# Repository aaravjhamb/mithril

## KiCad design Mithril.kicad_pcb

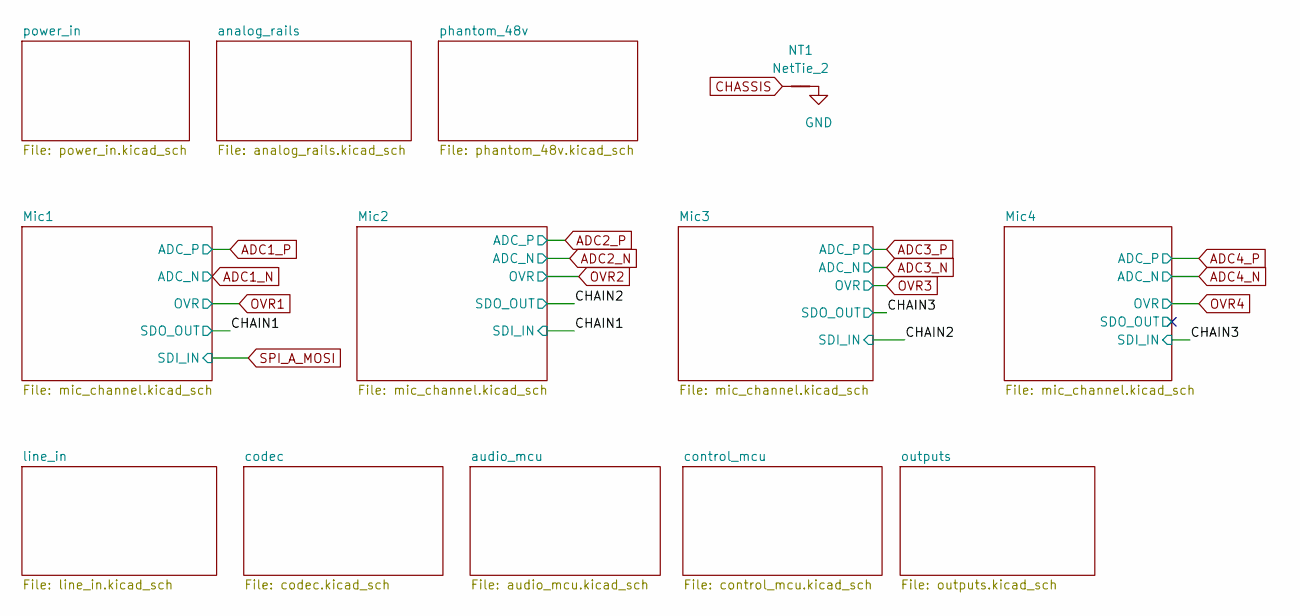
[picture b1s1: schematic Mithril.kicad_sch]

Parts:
NT1: NetTie_2; NetTie-2_SMD_Pad0.5mm

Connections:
CHASSIS: NT1.1; also elsewhere on the board
GND: NT1.2; also elsewhere on the board

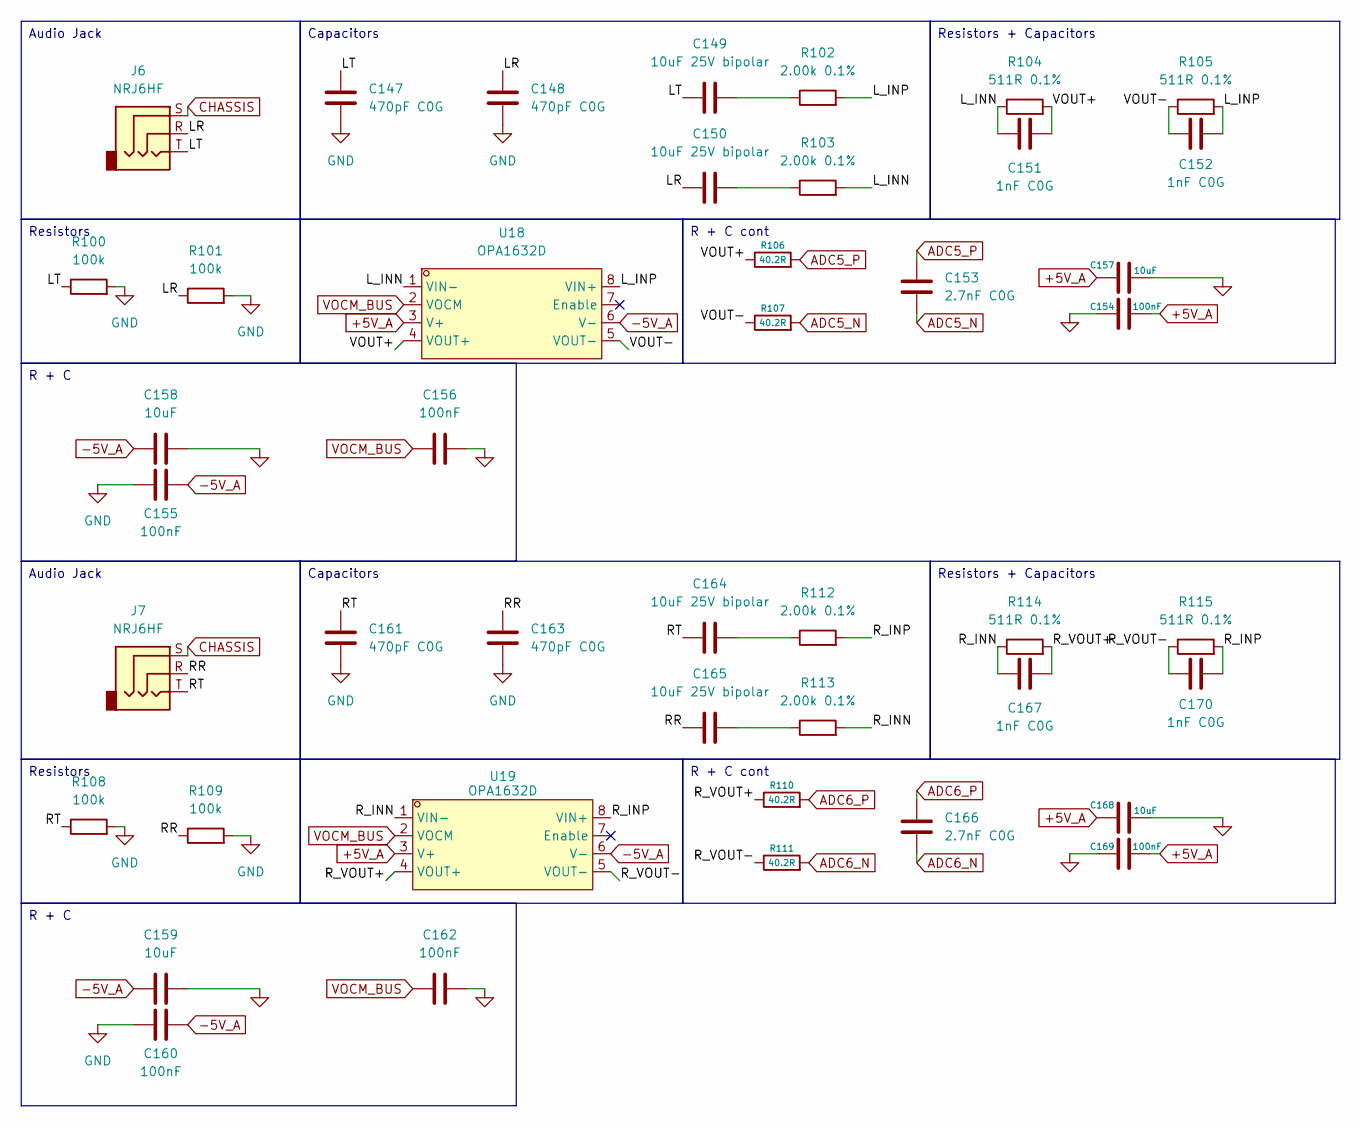
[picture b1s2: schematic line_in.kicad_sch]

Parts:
C147, C148, C161, C163: 470pF C0G; C_0603_1608Metric
C149, C150, C164, C165: 10uF 25V bipolar; CP_Elec_6.3x5.4
C151, C152, C167, C170: 1nF C0G; C_0603_1608Metric
C153, C166: 2.7nF C0G; C_0603_1608Metric
C154, C155, C156, C160, C162, C169: 100nF; C_0603_1608Metric
C157, C158, C159, C168: 10uF; C_0805_2012Metric
J6, J7: NRJ6HF; Jack_6.35mm_Neutrik_NRJ6HF_Horizontal
R100, R101, R108, R109: 100k; R_0603_1608Metric
R102, R103, R112, R113: 2.00k 0.1%; R_0603_1608Metric
R104, R105, R114, R115: 511R 0.1%; R_0603_1608Metric
R106, R107, R110, R111: 40.2R; R_0603_1608Metric
U18, U19: OPA1632D; SOIC-8_L4.9-W3.9-P1.27-LS6.0-BL; MPN OPA1632DR; LCSC Part C86715

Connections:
+5V_A: C154.2, C157.1, C168.1, C169.2, U18.3 (V+), U19.3 (V+); also elsewhere on the board
/line_in/LR: C148.1, C150.1, J6.R, R101.1
/line_in/LT: C147.1, C149.1, J6.T, R100.1
/line_in/L_INN: C151.1, R103.2, R104.1, U18.1 (VIN-)
/line_in/L_INP: C152.2, R102.2, R105.2, U18.8 (VIN+)
/line_in/RR: C163.1, C165.1, J7.R, R109.1
/line_in/RT: C161.1, C164.1, J7.T, R108.1
/line_in/R_INN: C167.1, R113.2, R114.1, U19.1 (VIN-)
/line_in/R_INP: C170.2, R112.2, R115.2, U19.8 (VIN+)
/line_in/R_VOUT+: C167.2, R110.1, R114.2, U19.4 (VOUT+)
/line_in/R_VOUT-: C170.1, R111.1, R115.1, U19.5 (VOUT-)
/line_in/VOUT+: C151.2, R104.2, R106.1, U18.4 (VOUT+)
/line_in/VOUT-: C152.1, R105.1, R107.1, U18.5 (VOUT-)
ADC5_N: C153.2, R107.2; also elsewhere on the board
ADC5_P: C153.1, R106.2; also elsewhere on the board
ADC6_N: C166.2, R111.2; also elsewhere on the board
ADC6_P: C166.1, R110.2; also elsewhere on the board
CHASSIS: J6.S, J7.S; also elsewhere on the board
GND: C147.2, C148.2, C154.1, C155.1, C156.2, C157.2, C158.2, C159.2, C160.1, C161.2, C162.2, C163.2, C168.2, C169.1, R100.2, R101.2, R108.2, R109.2; also elsewhere on the board
unnamed: C149.2, R102.1
unnamed: C150.2, R103.1
unnamed: C164.2, R112.1
unnamed: C165.2, R113.1
VOCM_BUS: C156.1, C162.1, U18.2 (VOCM), U19.2 (VOCM); also elsewhere on the board
−5V_A: C155.2, C158.1, C159.1, C160.2, U18.6 (V-), U19.6 (V-); also elsewhere on the board

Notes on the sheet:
Audio Jack
Capacitors
R + C cont
R + C
Resistors + Capacitors
Resistors

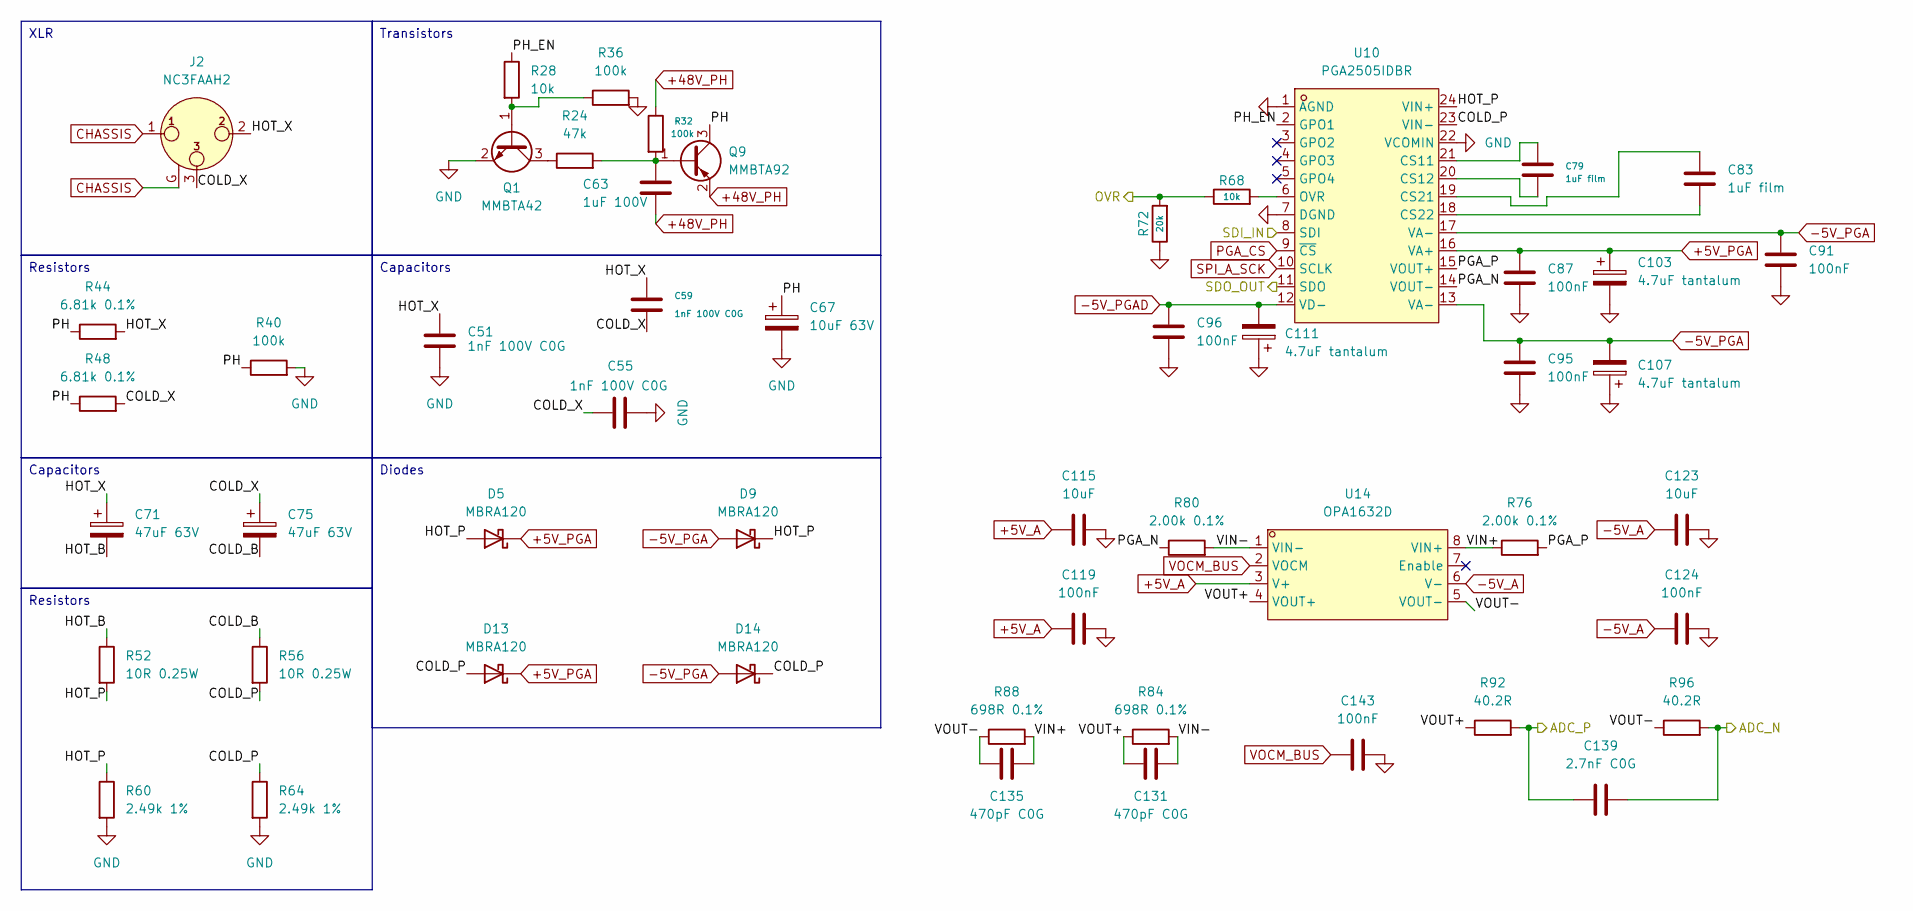
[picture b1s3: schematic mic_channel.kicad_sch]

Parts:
C51, C55, C59: 1nF 100V C0G; C_0603_1608Metric
C63: 1uF 100V; C_1206_3216Metric
C67: 10uF 63V; CP_Elec_6.3x7.7
C71, C75: 47uF 63V; CP_Elec_8x10.5
C79, C83: 1uF film; C_1210_3225Metric
C87, C91, C95, C96, C119, C124, C143: 100nF; C_0603_1608Metric
C103, C107, C111: 4.7uF tantalum; CP_EIA-3216-18_Kemet-A
C115, C123: 10uF; C_0805_2012Metric
C131, C135: 470pF C0G; C_0603_1608Metric
C139: 2.7nF C0G; C_0603_1608Metric
D5, D9, D13, D14: MBRA120; D_SMA
J2: NC3FAAH2; Jack_XLR_Neutrik_NC3FAAH2_Horizontal; LCSC Part C368522
Q1: MMBTA42; SOT-23
Q9: MMBTA92; SOT-23
R24: 47k; R_0805_2012Metric
R28: 10k; R_0805_2012Metric
R32, R36, R40: 100k; R_0805_2012Metric
R44, R48: 6.81k 0.1%; R_1206_3216Metric
R52, R56: 10R 0.25W; R_1206_3216Metric
R60, R64: 2.49k 1%; R_0603_1608Metric
R68: 10k; R_0603_1608Metric
R72: 20k; R_0603_1608Metric
R76, R80: 2.00k 0.1%; R_0603_1608Metric
R84, R88: 698R 0.1%; R_0603_1608Metric
R92, R96: 40.2R; R_0603_1608Metric
U10: PGA2505IDBR; SSOP-24_L8.2-W5.3-P0.65-LS7.8-BL; MPN PGA2505IDBR; LCSC Part C2877465
U14: OPA1632D; SOIC-8_L4.9-W3.9-P1.27-LS6.0-BL; MPN OPA1632DR; LCSC Part C86715

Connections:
+5V_A: C115.1, C119.1, U14.3 (V+); also elsewhere on the board
+5V_PGA: C87.1, C103.1, D5.1 (K), D13.1 (K), U10.16 (VA+); also elsewhere on the board
+48V_PH: C63.2, Q9.2 (E), R32.1; also elsewhere on the board
/CHAIN1: U10.11 (SDO); also elsewhere on the board
/Mic1/COLD_B: C75.2, R56.1
/Mic1/COLD_P: D13.2 (A), D14.1 (K), R56.2, R64.1, U10.23 (VIN-)
/Mic1/COLD_X: C55.1, C59.2, C75.1, J2.3, R48.2
/Mic1/HOT_B: C71.2, R52.1
/Mic1/HOT_P: D5.2 (A), D9.1 (K), R52.2, R60.1, U10.24 (VIN+)
/Mic1/HOT_X: C51.1, C59.1, C71.1, J2.2, R44.2
/Mic1/PGA_N: R80.1, U10.14 (VOUT-)
/Mic1/PGA_P: R76.2, U10.15 (VOUT+)
/Mic1/PH: C67.1, Q9.3 (C), R40.1, R44.1, R48.1
/Mic1/PH_EN: R28.1, U10.2 (GPO1)
/Mic1/VIN+: C135.1, R76.1, R88.2, U14.8 (VIN+)
/Mic1/VIN-: C131.2, R80.2, R84.2, U14.1 (VIN-)
/Mic1/VOUT+: C131.1, R84.1, R92.1, U14.4 (VOUT+)
/Mic1/VOUT-: C135.2, R88.1, R96.1, U14.5 (VOUT-)
ADC1_N: C139.2, R96.2; also elsewhere on the board
ADC1_P: C139.1, R92.2; also elsewhere on the board
CHASSIS: J2.1, J2.G; also elsewhere on the board
GND: C51.2, C55.2, C67.2, C87.2, C91.2, C95.2, C96.2, C103.2, C107.1, C111.1, C115.2, C119.2, C123.2, C124.2, C143.2, Q1.2 (E), R36.2, R40.2, R60.2, R64.2, R72.1, U10.1 (AGND), U10.7 (DGND), U10.22 (VCOMIN); also elsewhere on the board
unnamed: Q1.1 (B), R28.2, R36.1
unnamed: Q1.3 (C), R24.1
unnamed: C63.1, Q9.1 (B), R24.2, R32.2
unnamed: C79.1, U10.21 (CS11)
unnamed: C79.2, U10.20 (CS12)
unnamed: C83.1, U10.19 (CS21)
unnamed: C83.2, U10.18 (CS22)
unnamed: R68.2, U10.6 (OVR)
OVR1: R68.1, R72.2; also elsewhere on the board
PGA_CS: U10.9 (~CS); also elsewhere on the board
SPI_A_MOSI: U10.8 (SDI); also elsewhere on the board
SPI_A_SCK: U10.10 (SCLK); also elsewhere on the board
VOCM_BUS: C143.1, U14.2 (VOCM); also elsewhere on the board
−5V_A: C123.1, C124.1, U14.6 (V-); also elsewhere on the board
−5V_PGA: C91.1, C95.1, C107.2, D9.2 (A), D14.2 (A), U10.13 (VA-), U10.17 (VA-); also elsewhere on the board
−5V_PGAD: C96.1, C111.2, U10.12 (VD-); also elsewhere on the board

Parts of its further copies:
C52, C53, C54, C56, C57, C58, C60, C61, C62: 1nF 100V C0G; C_0603_1608Metric
C64, C65, C66: 1uF 100V; C_1206_3216Metric
C68, C69, C70: 10uF 63V; CP_Elec_6.3x7.7
C72, C73, C74, C76, C77, C78: 47uF 63V; CP_Elec_8x10.5
C80, C81, C82, C84, C85, C86: 1uF film; C_1210_3225Metric
C88, C89, C90, C92, C93, C94, C97, C98, C99, C100, C101, C102, C120, C121, C122, C126, C128, C130, C144, C145, C146: 100nF; C_0603_1608Metric
C104, C105, C106, C108, C109, C110, C112, C113, C114: 4.7uF tantalum; CP_EIA-3216-18_Kemet-A
C116, C117, C118, C125, C127, C129: 10uF; C_0805_2012Metric
C132, C133, C134, C136, C137, C138: 470pF C0G; C_0603_1608Metric
C140, C141, C142: 2.7nF C0G; C_0603_1608Metric
D6, D7, D8, D10, D11, D12, D15, D16, D17, D18, D19, D20: MBRA120; D_SMA
J3, J4, J5: NC3FAAH2; Jack_XLR_Neutrik_NC3FAAH2_Horizontal; LCSC Part C368522
Q2, Q3, Q4: MMBTA42; SOT-23
Q10, Q11, Q12: MMBTA92; SOT-23
R25, R26, R27: 47k; R_0805_2012Metric
R29, R30, R31: 10k; R_0805_2012Metric
R33, R34, R35, R37, R38, R39, R41, R42, R43: 100k; R_0805_2012Metric
R45, R46, R47, R49, R50, R51: 6.81k 0.1%; R_1206_3216Metric
R53, R54, R55, R57, R58, R59: 10R 0.25W; R_1206_3216Metric
R61, R62, R63, R65, R66, R67: 2.49k 1%; R_0603_1608Metric
R69, R70, R71: 10k; R_0603_1608Metric
R73, R74, R75: 20k; R_0603_1608Metric
R77, R78, R79, R81, R82, R83: 2.00k 0.1%; R_0603_1608Metric
R85, R86, R87, R89, R90, R91: 698R 0.1%; R_0603_1608Metric
R93, R94, R95, R97, R98, R99: 40.2R; R_0603_1608Metric
U11, U12, U13: PGA2505IDBR; SSOP-24_L8.2-W5.3-P0.65-LS7.8-BL; MPN PGA2505IDBR; LCSC Part C2877465
U15, U16, U17: OPA1632D; SOIC-8_L4.9-W3.9-P1.27-LS6.0-BL; MPN OPA1632DR; LCSC Part C86715

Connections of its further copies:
+5V_A: C116.1, C117.1, C118.1, C120.1, C121.1, C122.1, U15.3 (V+), U16.3 (V+), U17.3 (V+); also elsewhere on the board
+5V_PGA: C88.1, C89.1, C90.1, C104.1, C105.1, C106.1, D6.1 (K), D7.1 (K), D8.1 (K), D15.1 (K), D17.1 (K), D19.1 (K), U11.16 (VA+), U12.16 (VA+), U13.16 (VA+); also elsewhere on the board
+48V_PH: C64.2, C65.2, C66.2, Q10.2 (E), Q11.2 (E), Q12.2 (E), R33.1, R34.1, R35.1; also elsewhere on the board
/CHAIN1: U11.8 (SDI); also elsewhere on the board
/CHAIN2: U11.11 (SDO), U12.8 (SDI)
/CHAIN3: U12.11 (SDO), U13.8 (SDI)
/Mic2/COLD_B: C76.2, R57.1
/Mic2/COLD_P: D15.2 (A), D16.1 (K), R57.2, R65.1, U11.23 (VIN-)
/Mic2/COLD_X: C56.1, C60.2, C76.1, J3.3, R49.2
/Mic2/HOT_B: C72.2, R53.1
/Mic2/HOT_P: D6.2 (A), D10.1 (K), R53.2, R61.1, U11.24 (VIN+)
/Mic2/HOT_X: C52.1, C60.1, C72.1, J3.2, R45.2
/Mic2/PGA_N: R81.1, U11.14 (VOUT-)
/Mic2/PGA_P: R77.2, U11.15 (VOUT+)
/Mic2/PH: C68.1, Q10.3 (C), R41.1, R45.1, R49.1
/Mic2/PH_EN: R29.1, U11.2 (GPO1)
/Mic2/VIN+: C136.1, R77.1, R89.2, U15.8 (VIN+)
/Mic2/VIN-: C132.2, R81.2, R85.2, U15.1 (VIN-)
/Mic2/VOUT+: C132.1, R85.1, R93.1, U15.4 (VOUT+)
/Mic2/VOUT-: C136.2, R89.1, R97.1, U15.5 (VOUT-)
/Mic3/COLD_B: C77.2, R58.1
/Mic3/COLD_P: D17.2 (A), D18.1 (K), R58.2, R66.1, U12.23 (VIN-)
/Mic3/COLD_X: C57.1, C61.2, C77.1, J4.3, R50.2
/Mic3/HOT_B: C73.2, R54.1
/Mic3/HOT_P: D7.2 (A), D11.1 (K), R54.2, R62.1, U12.24 (VIN+)
/Mic3/HOT_X: C53.1, C61.1, C73.1, J4.2, R46.2
/Mic3/PGA_N: R82.1, U12.14 (VOUT-)
/Mic3/PGA_P: R78.2, U12.15 (VOUT+)
/Mic3/PH: C69.1, Q11.3 (C), R42.1, R46.1, R50.1
/Mic3/PH_EN: R30.1, U12.2 (GPO1)
/Mic3/VIN+: C137.1, R78.1, R90.2, U16.8 (VIN+)
/Mic3/VIN-: C133.2, R82.2, R86.2, U16.1 (VIN-)
/Mic3/VOUT+: C133.1, R86.1, R94.1, U16.4 (VOUT+)
/Mic3/VOUT-: C137.2, R90.1, R98.1, U16.5 (VOUT-)
/Mic4/COLD_B: C78.2, R59.1
/Mic4/COLD_P: D19.2 (A), D20.1 (K), R59.2, R67.1, U13.23 (VIN-)
/Mic4/COLD_X: C58.1, C62.2, C78.1, J5.3, R51.2
/Mic4/HOT_B: C74.2, R55.1
/Mic4/HOT_P: D8.2 (A), D12.1 (K), R55.2, R63.1, U13.24 (VIN+)
/Mic4/HOT_X: C54.1, C62.1, C74.1, J5.2, R47.2
/Mic4/PGA_N: R83.1, U13.14 (VOUT-)
/Mic4/PGA_P: R79.2, U13.15 (VOUT+)
/Mic4/PH: C70.1, Q12.3 (C), R43.1, R47.1, R51.1
/Mic4/PH_EN: R31.1, U13.2 (GPO1)
/Mic4/SDO_OUT: U13.11 (SDO)
/Mic4/VIN+: C138.1, R79.1, R91.2, U17.8 (VIN+)
/Mic4/VIN-: C134.2, R83.2, R87.2, U17.1 (VIN-)
/Mic4/VOUT+: C134.1, R87.1, R95.1, U17.4 (VOUT+)
/Mic4/VOUT-: C138.2, R91.1, R99.1, U17.5 (VOUT-)
ADC2_N: C140.2, R97.2; also elsewhere on the board
ADC2_P: C140.1, R93.2; also elsewhere on the board
ADC3_N: C141.2, R98.2; also elsewhere on the board
ADC3_P: C141.1, R94.2; also elsewhere on the board
ADC4_N: C142.2, R99.2; also elsewhere on the board
ADC4_P: C142.1, R95.2; also elsewhere on the board
CHASSIS: J3.1, J3.G, J4.1, J4.G, J5.1, J5.G; also elsewhere on the board
GND: C52.2, C53.2, C54.2, C56.2, C57.2, C58.2, C68.2, C69.2, C70.2, C88.2, C89.2, C90.2, C92.2, C93.2, C94.2, C97.2, C98.2, C99.2, C100.2, C101.2, C102.2, C104.2, C105.2, C106.2, C108.1, C109.1, C110.1, C112.1, C113.1, C114.1, C116.2, C117.2, C118.2, C120.2, C121.2, C122.2, C125.2, C126.2, C127.2, C128.2, C129.2, C130.2, C144.2, C145.2, C146.2, Q2.2 (E), Q3.2 (E), Q4.2 (E), R37.2, R38.2, R39.2, R41.2, R42.2, R43.2, R61.2, R62.2, R63.2, R65.2, R66.2, R67.2, R73.1, R74.1, R75.1, U11.1 (AGND), U11.7 (DGND), U11.22 (VCOMIN), U12.1 (AGND), U12.7 (DGND), U12.22 (VCOMIN), U13.1 (AGND), U13.7 (DGND), U13.22 (VCOMIN); also elsewhere on the board
unnamed: Q2.1 (B), R29.2, R37.1
unnamed: Q2.3 (C), R25.1
unnamed: Q3.1 (B), R30.2, R38.1
unnamed: Q3.3 (C), R26.1
unnamed: Q4.1 (B), R31.2, R39.1
unnamed: Q4.3 (C), R27.1
unnamed: C64.1, Q10.1 (B), R25.2, R33.2
unnamed: C65.1, Q11.1 (B), R26.2, R34.2
unnamed: C66.1, Q12.1 (B), R27.2, R35.2
unnamed: C80.1, U11.21 (CS11)
unnamed: C80.2, U11.20 (CS12)
unnamed: C84.1, U11.19 (CS21)
unnamed: C84.2, U11.18 (CS22)
unnamed: R69.2, U11.6 (OVR)
unnamed: C81.1, U12.21 (CS11)
unnamed: C81.2, U12.20 (CS12)
unnamed: C85.1, U12.19 (CS21)
unnamed: C85.2, U12.18 (CS22)
unnamed: R70.2, U12.6 (OVR)
unnamed: C82.1, U13.21 (CS11)
unnamed: C82.2, U13.20 (CS12)
unnamed: C86.1, U13.19 (CS21)
unnamed: C86.2, U13.18 (CS22)
unnamed: R71.2, U13.6 (OVR)
OVR2: R69.1, R73.2; also elsewhere on the board
OVR3: R70.1, R74.2; also elsewhere on the board
OVR4: R71.1, R75.2; also elsewhere on the board
PGA_CS: U11.9 (~CS), U12.9 (~CS), U13.9 (~CS); also elsewhere on the board
SPI_A_SCK: U11.10 (SCLK), U12.10 (SCLK), U13.10 (SCLK); also elsewhere on the board
VOCM_BUS: C144.1, C145.1, C146.1, U15.2 (VOCM), U16.2 (VOCM), U17.2 (VOCM); also elsewhere on the board
−5V_A: C125.1, C126.1, C127.1, C128.1, C129.1, C130.1, U15.6 (V-), U16.6 (V-), U17.6 (V-); also elsewhere on the board
−5V_PGA: C92.1, C93.1, C94.1, C97.1, C99.1, C101.1, C108.2, C109.2, C110.2, D10.2 (A), D11.2 (A), D12.2 (A), D16.2 (A), D18.2 (A), D20.2 (A), U11.13 (VA-), U11.17 (VA-), U12.13 (VA-), U12.17 (VA-), U13.13 (VA-), U13.17 (VA-); also elsewhere on the board
−5V_PGAD: C98.1, C100.1, C102.1, C112.2, C113.2, C114.2, U11.12 (VD-), U12.12 (VD-), U13.12 (VD-); also elsewhere on the board

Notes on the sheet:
Transistors
Diodes
Capacitors
XLR
Resistors
Resistors
Capacitors

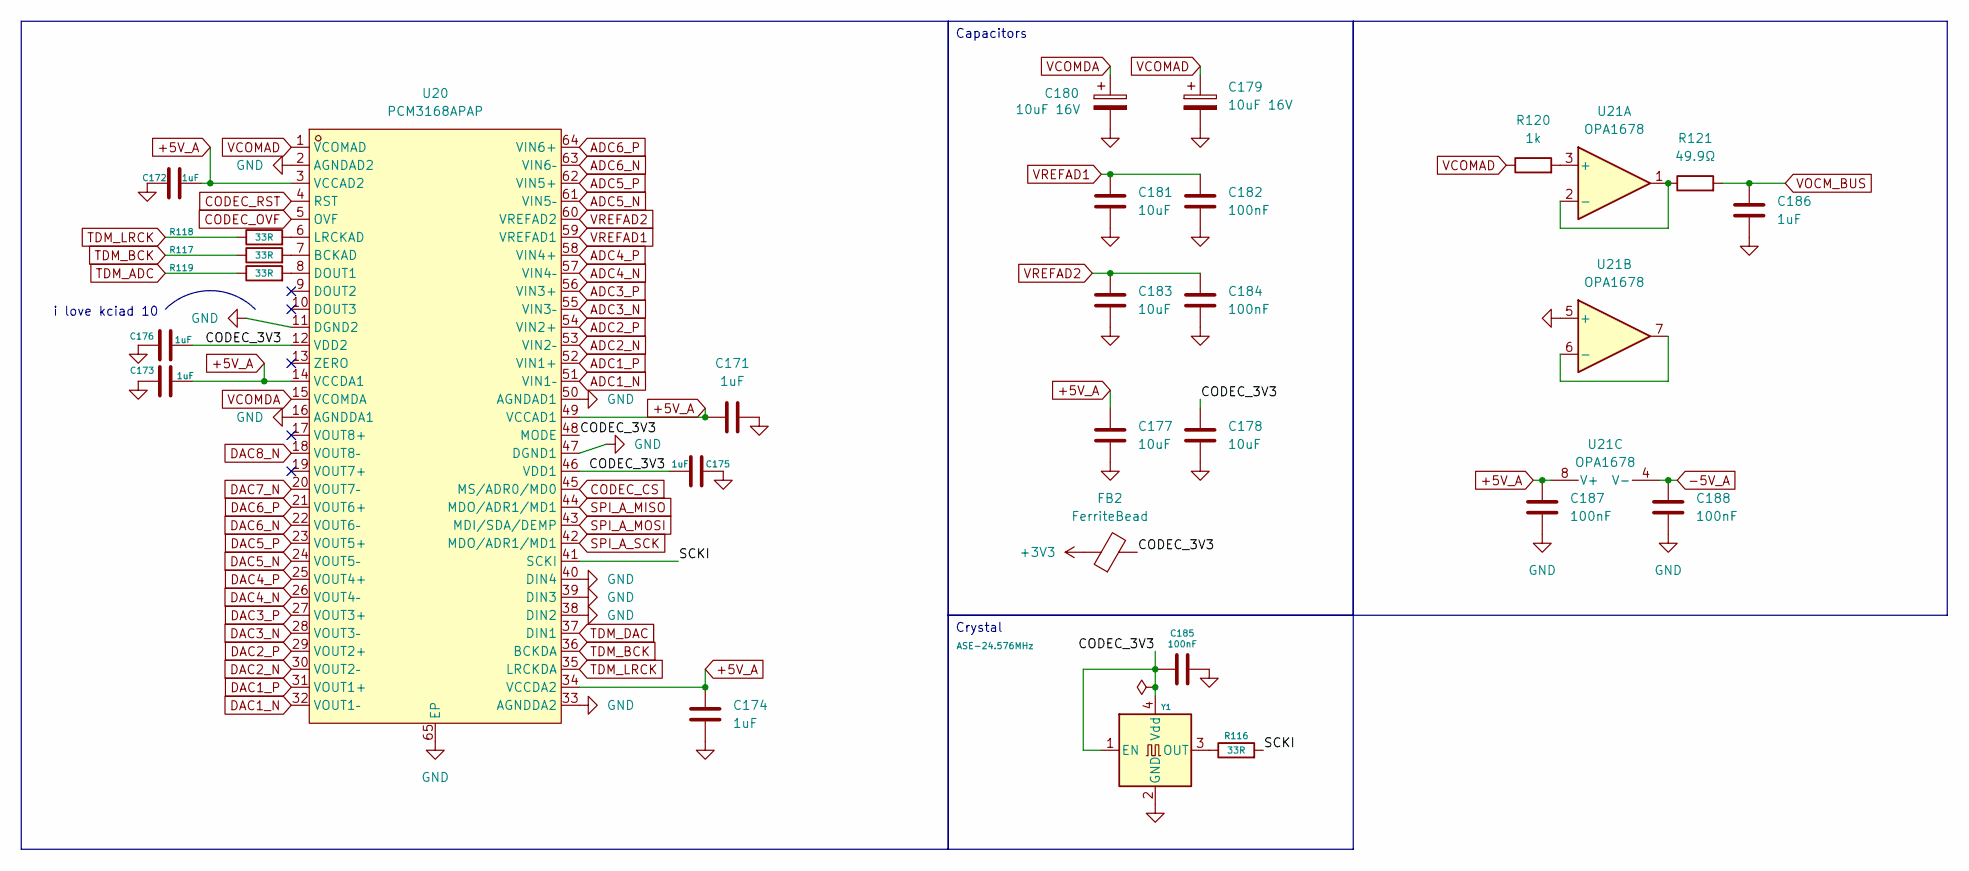
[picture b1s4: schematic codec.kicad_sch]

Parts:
C171, C172, C173, C174, C175, C176, C186: 1uF; C_0603_1608Metric
C177, C178, C181, C183: 10uF; C_0805_2012Metric
C179, C180: 10uF 16V; CP_EIA-3216-18_Kemet-A
C182, C184, C185, C187, C188: 100nF; C_0603_1608Metric
FB2: FerriteBead; L_0603_1608Metric
R116, R117, R118, R119: 33R; R_0603_1608Metric
R120: 1k; R_0603_1608Metric
R121: 49.9Ω; R_0603_1608Metric
U20: PCM3168APAP; HTQFP-64_L10.0-W10.0-P0.50-LS12.0-BL-EP5.9; MPN PCM3168APAP; LCSC Part C1521535
U21: OPA1678; SOIC-8_3.9x4.9mm_P1.27mm
Y1: ASE-24.576MHz; Oscillator_SMD_Abracon_ASE-4Pin_3.2x2.5mm

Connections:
+3V3: FB2.1; also elsewhere on the board
+5V_A: C171.1, C172.2, C173.1, C174.1, C177.1, C187.1, U20.3 (VCCAD2), U20.14 (VCCDA1), U20.34 (VCCDA2), U20.49 (VCCAD1), U21.8 (V+); also elsewhere on the board
/codec/CODEC_3V3: C175.1, C176.2, C178.1, C185.1, FB2.2, U20.12 (VDD2), U20.46 (VDD1), U20.48 (MODE), Y1.1 (EN), Y1.4 (Vdd)
/codec/SCKI: R116.2, U20.41 (SCKI)
ADC1_N: U20.51 (VIN1–); also elsewhere on the board
ADC1_P: U20.52 (VIN1+); also elsewhere on the board
ADC2_N: U20.53 (VIN2–); also elsewhere on the board
ADC2_P: U20.54 (VIN2+); also elsewhere on the board
ADC3_N: U20.55 (VIN3–); also elsewhere on the board
ADC3_P: U20.56 (VIN3+); also elsewhere on the board
ADC4_N: U20.57 (VIN4–); also elsewhere on the board
ADC4_P: U20.58 (VIN4+); also elsewhere on the board
ADC5_N: U20.61 (VIN5–); also elsewhere on the board
ADC5_P: U20.62 (VIN5+); also elsewhere on the board
ADC6_N: U20.63 (VIN6–); also elsewhere on the board
ADC6_P: U20.64 (VIN6+); also elsewhere on the board
CODEC_CS: U20.45 (MS/ADR0/MD0); also elsewhere on the board
CODEC_OVF: U20.5 (OVF); also elsewhere on the board
CODEC_RST: U20.4 (RST); also elsewhere on the board
DAC1_N: U20.32 (VOUT1–); also elsewhere on the board
DAC1_P: U20.31 (VOUT1+); also elsewhere on the board
DAC2_N: U20.30 (VOUT2–); also elsewhere on the board
DAC2_P: U20.29 (VOUT2+); also elsewhere on the board
DAC3_N: U20.28 (VOUT3–); also elsewhere on the board
DAC3_P: U20.27 (VOUT3+); also elsewhere on the board
DAC4_N: U20.26 (VOUT4–); also elsewhere on the board
DAC4_P: U20.25 (VOUT4+); also elsewhere on the board
DAC5_N: U20.24 (VOUT5–); also elsewhere on the board
DAC5_P: U20.23 (VOUT5+); also elsewhere on the board
DAC6_N: U20.22 (VOUT6–); also elsewhere on the board
DAC6_P: U20.21 (VOUT6+); also elsewhere on the board
DAC7_N: U20.20 (VOUT7–); also elsewhere on the board
DAC8_N: U20.18 (VOUT8–); also elsewhere on the board
GND: C171.2, C172.1, C173.2, C174.2, C175.2, C176.1, C177.2, C178.2, C179.2, C180.2, C181.2, C182.2, C183.2, C184.2, C185.2, C186.2, C187.2, C188.2, U20.2 (AGNDAD2), U20.11 (DGND2), U20.16 (AGNDDA1), U20.33 (AGNDDA2), U20.38 (DIN2), U20.39 (DIN3), U20.40 (DIN4), U20.47 (DGND1), U20.50 (AGNDAD1), U20.65 (EP), U21.5 (+), Y1.2 (GND); also elsewhere on the board
unnamed: R117.2, U20.7 (BCKAD)
unnamed: R119.2, U20.8 (DOUT1)
unnamed: R118.2, U20.6 (LRCKAD)
unnamed: R120.2, U21.3 (+)
unnamed: R121.1, U21.1, U21.2 (-)
unnamed: U21.6 (-), U21.7
unnamed: R116.1, Y1.3 (OUT)
SPI_A_MISO: U20.44 (MDO/ADR1/MD1); also elsewhere on the board
SPI_A_MOSI: U20.43 (MDI/SDA/DEMP); also elsewhere on the board
SPI_A_SCK: U20.42 (MDO/ADR1/MD1); also elsewhere on the board
TDM_ADC: R119.1; also elsewhere on the board
TDM_BCK: R117.1, U20.36 (BCKDA); also elsewhere on the board
TDM_DAC: U20.37 (DIN1); also elsewhere on the board
TDM_LRCK: R118.1, U20.35 (LRCKDA); also elsewhere on the board
VCOMAD: C179.1, R120.1, U20.1 (VCOMAD)
VCOMDA: C180.1, U20.15 (VCOMDA)
VOCM_BUS: C186.1, R121.2; also elsewhere on the board
VREFAD1: C181.1, C182.1, U20.59 (VREFAD1)
VREFAD2: C183.1, C184.1, U20.60 (VREFAD2)
−5V_A: C188.1, U21.4 (V-); also elsewhere on the board

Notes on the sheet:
i love kciad 10
Capacitors
Crystal

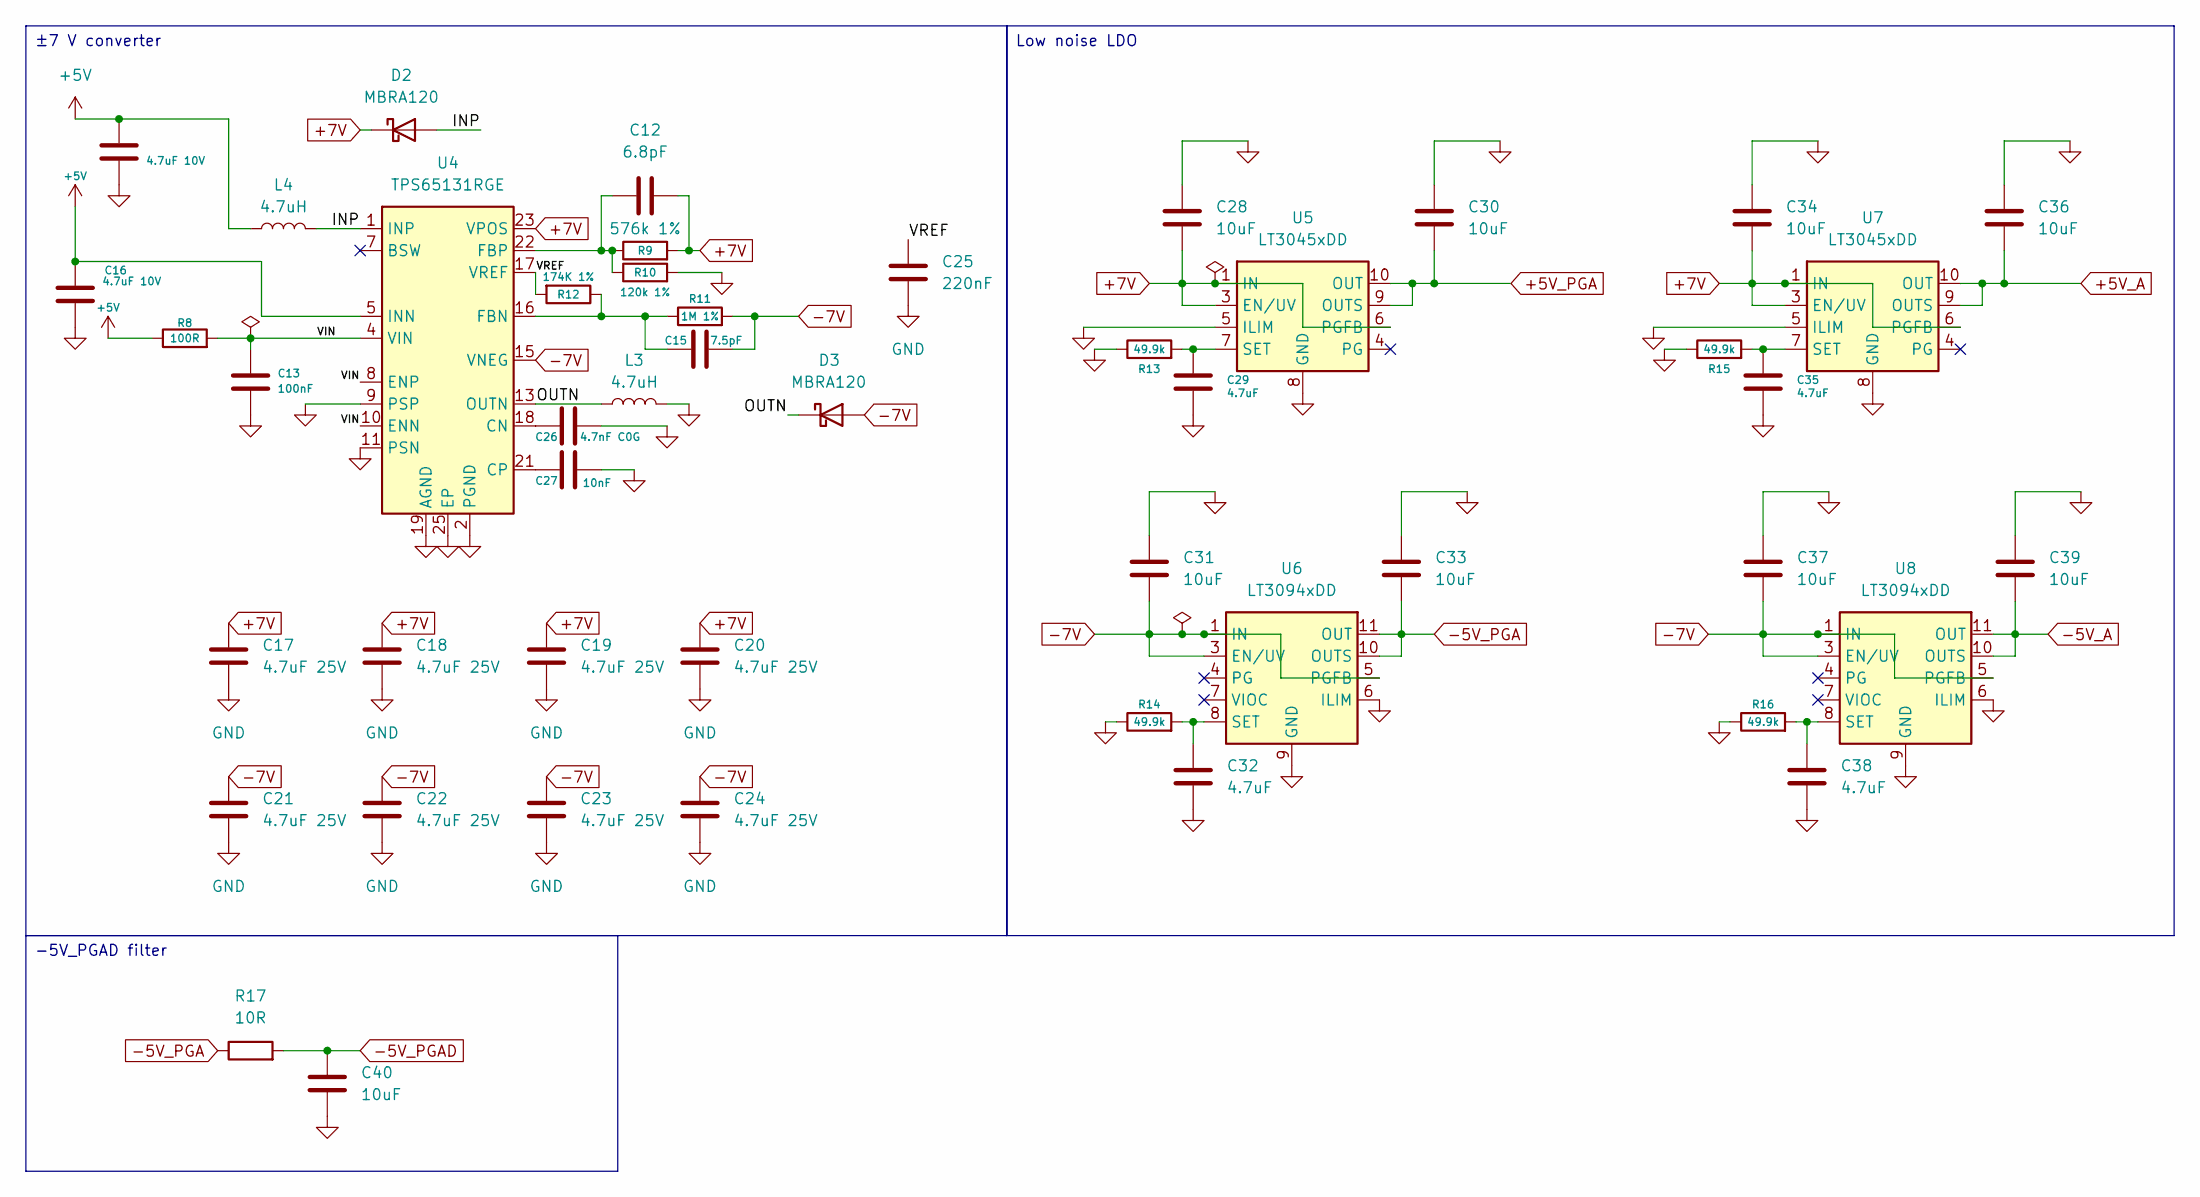
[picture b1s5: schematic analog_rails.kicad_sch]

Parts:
C12: 6.8pF; C_0603_1608Metric
C13: 100nF; C_0603_1608Metric
C14, C16: 4.7uF 10V; C_0805_2012Metric
C15: 7.5pF; C_0603_1608Metric
C17, C18, C19, C20, C21, C22, C23, C24: 4.7uF 25V; C_0805_2012Metric
C25: 220nF; C_0603_1608Metric
C26: 4.7nF C0G; C_0603_1608Metric
C27: 10nF; C_0603_1608Metric
C28, C30, C31, C33, C34, C36, C37, C39, C40: 10uF; C_0805_2012Metric
C29, C32, C35, C38: 4.7uF; C_0805_2012Metric
D2, D3: MBRA120; D_SMA
L3, L4: 4.7uH; L_Sunlord_MWSA0518S; LCSC Part C408347
R8: 100R; R_0603_1608Metric
R9: 576k 1%; R_0603_1608Metric
R10: 120k 1%; R_0603_1608Metric
R11: 1M 1%; R_0603_1608Metric
R12: 174K 1%; R_0603_1608Metric
R13, R14, R15, R16: 49.9k; R_0603_1608Metric
R17: 10R; R_0603_1608Metric
U4: TPS65131RGE; VQFN-24-1EP_4x4mm_P0.5mm_EP2.45x2.45mm_ThermalVias
U5, U7: LT3045xDD; DFN-10-1EP_3x3mm_P0.5mm_EP1.65x2.38mm
U6, U8: LT3094xDD; DFN-12-1EP_3x3mm_P0.45mm_EP1.65x2.38mm_ThermalVias

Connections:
+5V: C14.1, C16.1, L4.1, R8.1, U4.5 (INN), U4.6 (INN); also elsewhere on the board
+5V_A: C36.2, U7.9 (OUTS), U7.10 (OUT); also elsewhere on the board
+5V_PGA: C30.2, U5.9 (OUTS), U5.10 (OUT); also elsewhere on the board
+7V: C12.2, C17.1, C18.1, C19.1, C20.1, C28.2, C34.2, D2.1 (K), R9.2, U4.23 (VPOS), U5.1 (IN), U5.2 (IN), U5.3 (EN/UV), U5.6 (PGFB), U7.1 (IN), U7.2 (IN), U7.3 (EN/UV), U7.6 (PGFB)
-7V: C15.2, C21.1, C22.1, C23.1, C24.1, C31.2, C37.2, D3.2 (A), R11.2, U4.15 (VNEG), U6.1 (IN), U6.2 (IN), U6.3 (EN/UV), U6.5 (PGFB), U6.13 (IN), U8.1 (IN), U8.2 (IN), U8.3 (EN/UV), U8.5 (PGFB), U8.13 (IN)
/analog_rails/INP: D2.2 (A), L4.2, U4.1 (INP), U4.24 (INP)
/analog_rails/OUTN: D3.1 (K), L3.1, U4.13 (OUTN), U4.14 (OUTN)
/analog_rails/VIN: C13.1, R8.2, U4.4 (VIN), U4.8 (ENP), U4.10 (ENN)
/analog_rails/VREF: C25.1, R12.2, U4.17 (VREF)
GND: C13.2, C14.2, C16.2, C17.2, C18.2, C19.2, C20.2, C21.2, C22.2, C23.2, C24.2, C25.2, C26.2, C27.2, C28.1, C29.2, C30.1, C31.1, C32.2, C33.1, C34.1, C35.2, C36.1, C37.1, C38.2, C39.1, C40.2, L3.2, R10.2, R13.1, R14.1, R15.1, R16.1, U4.2 (PGND), U4.3 (PGND), U4.9 (PSP), U4.11 (PSN), U4.19 (AGND), U4.25 (EP), U5.5 (ILIM), U5.8 (GND), U5.11 (GND), U6.6 (ILIM), U6.9 (GND), U7.5 (ILIM), U7.8 (GND), U7.11 (GND), U8.6 (ILIM), U8.9 (GND); also elsewhere on the board
unnamed: C26.1, U4.18 (CN)
unnamed: C27.1, U4.21 (CP)
unnamed: C15.1, R11.1, R12.1, U4.16 (FBN)
unnamed: C12.1, R9.1, R10.1, U4.22 (FBP)
unnamed: C29.1, R13.2, U5.7 (SET)
unnamed: C32.1, R14.2, U6.8 (SET)
unnamed: C35.1, R15.2, U7.7 (SET)
unnamed: C38.1, R16.2, U8.8 (SET)
−5V_A: C39.2, U8.10 (OUTS), U8.11 (OUT), U8.12 (OUT); also elsewhere on the board
−5V_PGA: C33.2, R17.1, U6.10 (OUTS), U6.11 (OUT), U6.12 (OUT); also elsewhere on the board
−5V_PGAD: C40.1, R17.2; also elsewhere on the board

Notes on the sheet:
Low noise LDO
-5V_PGAD filter
±7 V converter

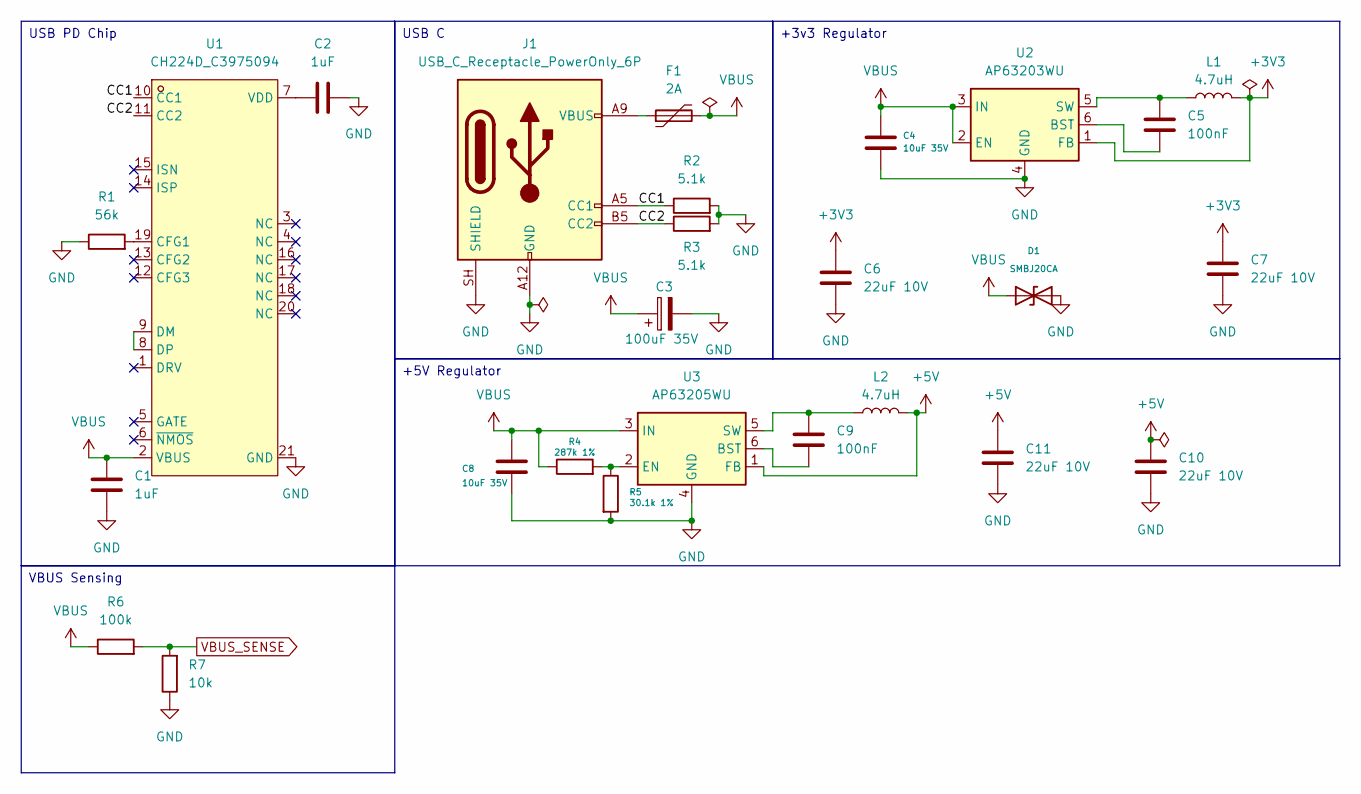
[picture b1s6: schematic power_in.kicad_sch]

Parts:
C1, C2: 1uF; C_0603_1608Metric
C3: 100uF 35V; CP_Elec_6.3x7.7
C4, C8: 10uF 35V; C_1206_3216Metric
C5, C9: 100nF; C_0603_1608Metric
C6, C7, C10, C11: 22uF 10V; C_1206_3216Metric
D1: SMBJ20CA; D_SMB
F1: 2A; Fuse_1812_4532Metric
J1: USB_C_Receptacle_PowerOnly_6P; USB-C-SMD_HC-TYPE-C-6P-01A; LCSC Part C2894893
L1, L2: 4.7uH; L_Sunlord_MWSA0518S; LCSC Part C408347
R1: 56k; R_0603_1608Metric
R2, R3: 5.1k; R_0603_1608Metric
R4: 287k 1%; R_0603_1608Metric
R5: 30.1k 1%; R_0603_1608Metric
R6: 100k; R_0603_1608Metric
R7: 10k; R_0603_1608Metric
U1: CH224D_C3975094; QFN-20_L3.0-W3.0-P0.40-BL-EP1.7; MPN CH224D; LCSC Part C3975094
U2: AP63203WU; TSOT-23-6
U3: AP63205WU; TSOT-23-6

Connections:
+3V3: C6.1, C7.1, L1.2, U2.1 (FB); also elsewhere on the board
+5V: C10.1, C11.1, L2.2, U3.1 (FB); also elsewhere on the board
/power_in/CC1: J1.A5 (CC1), R2.1, U1.10 (CC1)
/power_in/CC2: J1.B5 (CC2), R3.1, U1.11 (CC2)
GND: C1.2, C2.2, C3.2, C4.2, C6.2, C7.2, C8.2, C10.2, C11.2, D1.2 (A2), J1.A12 (GND), J1.B12 (GND), J1.SH (SHIELD), R1.1, R2.2, R3.2, R5.2, R7.1, U1.21 (GND), U2.4 (GND), U3.4 (GND); also elsewhere on the board
unnamed: F1.1, J1.A9 (VBUS), J1.B9 (VBUS)
unnamed: R1.2, U1.19 (CFG1)
unnamed: U1.8 (DP), U1.9 (DM)
unnamed: C2.1, U1.7 (VDD)
unnamed: C5.1, U2.6 (BST)
unnamed: C5.2, L1.1, U2.5 (SW)
unnamed: C9.2, U3.6 (BST)
unnamed: R4.2, R5.1, U3.2 (EN)
unnamed: C9.1, L2.1, U3.5 (SW)
VBUS: C1.1, C3.1, C4.1, C8.1, D1.1 (A1), F1.2, R4.1, R6.1, U1.2 (VBUS), U2.2 (EN), U2.3 (IN), U3.3 (IN); also elsewhere on the board
VBUS_SENSE: R6.2, R7.2; also elsewhere on the board

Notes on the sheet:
+3v3 Regulator
USB PD Chip
+5V Regulator
VBUS Sensing
USB C
